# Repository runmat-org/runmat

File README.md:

<h1 align="center">RunMat</h1>

<p align="center">
  <strong>MATLAB-compatible runtime for fast GPU-accelerated math.</strong>
</p>

<p align="center">

</p>

<p align="center">
  <a href="https://runmat.com/sandbox"><strong>Try RunMat in your browser</strong></a>
  |
  <a href="https://runmat.com/download">Download RunMat Desktop</a>
  |
  <a href="https://runmat.com/docs">Docs</a>
  |
  <a href="docs/CHANGELOG.md">Changelog</a>
  |
  <a href="benchmarks/README.md">Benchmarks</a>
</p>

RunMat is a source-available, high-performance runtime designed for numerical computing using MATLAB-style syntax. It is built in Rust and provides a multi-tiered execution model that targets both CPU and GPU hardware without requiring manual management of tensor allocations and movement.

RunMat runs MATLAB-syntax `.m` files with automatic operation fusion, a high-performance compiler, and a cross-platform GPU backend powered by wgpu.

RunMat is free for eligible individuals, education, open-source projects and smaller organizations under the [RunMat Free Use grant](FREE-USE.md). Simulation allowances and subscription features are described on the [pricing page](https://runmat.com/pricing).

Key Capabilities:

- MATLAB Compatibility: Supports MATLAB-syntax scripts and projects, including arrays, functions, classes, packages, and [2,300+ documented built-in functions](https://runmat.com/docs/reference/builtins).
- Native Compilation: [Compile `.m` scripts into standalone native executables](https://runmat.com/docs/runtime/getting-started/cli#compile) with `runmat compile`.
- Code Checks and Tests: [Check code without executing it](https://runmat.com/docs/runtime/getting-started/cli#check) with `runmat check`, and [run MATLAB-style script, function, and class tests](https://runmat.com/docs/runtime/getting-started/cli#test-projects) with `runmat test`.
- Integer Support: Work with signed and unsigned integer types from 8 to 64 bits.
- Project Packages: [Manage dependencies and lockfiles](https://runmat.com/docs/runtime/packages) for reproducible MATLAB-syntax projects with the CLI.
- Automatic Fusion: Builds an internal graph of array operations to fuse elementwise math and reductions into optimized kernels 
- Tiered Execution: Combines a fast-startup VM interpreter with a JIT (based on Cranelift) for hot code paths
- Cross-Platform GPU: Transparently offloads workloads to Metal, DirectX 12, Vulkan, or WebGPU
- Strong Static Analysis: Type/shape inference, definite assignment, and other static analysis passes are run before execution to optimize the execution plan.
- Async Runtime: Built on Rust futures, allowing non-blocking execution in web environments, CLI tools and headless pipelines
- Integrated Plotting: Features an interactive GPU-accelerated 2D/3D plotting engine supporting 30+ plot types

Explore the [MATLAB compatibility guide](https://runmat.com/docs/runtime/matlab-compatibility) for supported language features, or use `runmat check analysis.m` to check your code before running it.

## Quick Start

The quickest way to get started is to [open the RunMat Sandbox](https://runmat.com/sandbox) and run code in your browser—no installation required. To work with local files, download [RunMat Desktop](https://runmat.com/download).

Alternatively, you can install the CLI:

```bash
# Linux/macOS
curl -fsSL https://runmat.com/install.sh | sh

# Windows PowerShell
iwr https://runmat.com/install.ps1 | iex
```

Create a script `hello.m`:

```matlab
disp("Hello, World!");
A = magic(3);
disp(sum(A));
```

Run the script:

```bash
runmat hello.m
```

See [Hello World](https://runmat.com/docs/runtime/getting-started/hello-world) for more examples, and the [Command Line Interface](https://runmat.com/docs/runtime/getting-started/cli) for the full command surface.

## Other Installation Options

```bash
# Homebrew (macOS/Linux)
brew install runmat-org/tap/runmat

# Cargo (Rust)
cargo install runmat --features gui

# Build from source
git clone https://github.com/runmat-org/runmat.git && cd runmat
cargo build -p runmat --release --features gui
```

## CLI

The CLI can run local scripts or named project entrypoints - on local or remote projects.

```bash
runmat analysis.m

# which is shorthand for:

runmat run analysis.m
```

Check an existing script, run your project's tests, or compile a script into a standalone native executable:

```bash
# Check code without executing it
runmat check analysis.m

# Run the project's MATLAB-style tests
runmat test

# Compile a script into a native executable
runmat compile analysis.m -o analysis
```

See [code checking](https://runmat.com/docs/runtime/getting-started/cli#check), [project tests](https://runmat.com/docs/runtime/getting-started/cli#test-projects), and [native compilation](https://runmat.com/docs/runtime/getting-started/cli#compile) for options and examples.

Projects can define named entrypoints in `runmat.toml`:

```toml
[package]
name = "demo"

[entrypoints.main]
path = "src/main.m"
```

Run the entrypoint:

```bash
runmat run main
```

### Project Testing and CI

Produce JUnit reports for CI and collect LCOV coverage:

```bash
runmat test --report junit
runmat test --coverage --coverage-format lcov
```

The test runner supports MATLAB-style script, function, and class tests, with name and tag filters, cancellation, and JSON, JUnit, or TAP reports. See [project testing](https://runmat.com/docs/runtime/getting-started/cli#test-projects).

### Cloud Project Files

To run a script in a remote project backend, ensure you are authenticated and have selected a project:

```bash
runmat login

# or explicitly specify the server URL

runmat login --server https://api.runmat.com

runmat project select <project-id>
```

And then run the script:

```bash
runmat remote run /scripts/analysis.m
```

The script is executed locally with the remote filesystem provider mounted into the runtime's filesystem abstraction. This means that mutations to the filesystem are persisted to the remote project, but the script runs locally.

For the full command surface, see [Command Line Interface](https://runmat.com/docs/runtime/getting-started/cli).

## TypeScript And WebAssembly

The `runmat` npm package embeds the runtime in browser, worker, Electron, and Node-based hosts.

```bash
npm install runmat
```

```ts
import { initRunMat } from "runmat";

const session = await initRunMat();

const result = await session.executeRequest({
  source: {
    kind: "text",
    name: "<repl>",
    text: "A = magic(3); disp(A)"
  }
});

console.log(result.stdout);
console.log(result.workspace.values);

session.dispose();
```

The TypeScript API includes session execution, workspace snapshots, lazy variable materialization, filesystem providers, plotting surfaces, stdout subscriptions, runtime diagnostics, and GPU status reporting.

See [bindings/ts/README.md](bindings/ts/README.md) and [WASM & TypeScript/JavaScript](docs/wasm/index.md).

## What Is In This Repository

| Area | Crates and paths |
| --- | --- |
| Language frontend | `runmat-lexer`, `runmat-parser`, `runmat-hir`, `runmat-mir`, `runmat-static-analysis` |
| Execution | `runmat-core`, `runmat-vm`, `runmat-runtime`, `runmat-builtins` |
| Native execution and compilation | `runmat-native-executor`, `runmat-jit`, `runmat-native-codegen`, `runmat-aot` |
| GPU acceleration | `runmat-accelerate`, `runmat-accelerate-api` |
| Memory management | `runmat-gc`, `runmat-gc-api` |
| Plotting | `runmat-plot` |
| Filesystem and config | `runmat-filesystem`, `runmat-config` |
| CLI and remote services | `runmat-cli`, `runmat-server-client` |
| Browser bindings | `runmat-wasm`, `bindings/ts` |
| Tooling | `runmat-lsp`, `runmat-telemetry`, `runmat-logging` |

The runtime is host-neutral. The CLI, Desktop, WASM bindings, and LSP all submit source through the same session/execution boundary and consume structured results.

## Runtime Highlights

- MATLAB-style source execution for scripts, functions, packages, imports, `classdef`, indexing, cells, structs, exceptions, and common language constructs.
- Built-in functions for array operations, linear algebra, tables, plotting, file I/O, optimization, and ODEs, plus control design with [`lqr`](https://runmat.com/docs/reference/builtins/lqr), linear regression with [`fitlm`](https://runmat.com/docs/reference/builtins/fitlm), spectral analysis with [`pwelch`](https://runmat.com/docs/reference/builtins/pwelch), and symbolic variables with [`syms`](https://runmat.com/docs/reference/builtins/syms).
- A bytecode VM for predictable startup and a Cranelift JIT for hot execution paths.
- GPU acceleration through fusion, auto-offload decisions, and `wgpu` backends for Metal, Vulkan, DirectX 12, and WebGPU.
- Interactive 2D and 3D plotting with figure handles, subplot state, labels, legends, export, replay, and browser canvas integration.
- Session APIs for REPLs, notebooks, editors, browser sandboxes, and remote filesystem-backed projects.
- TypeScript bindings with filesystem providers for memory, IndexedDB, and remote HTTP-backed workspaces.

### Validation

RunMat tests cover parsing and language semantics, runtime functions, CPU/GPU execution, and browser/WASM behavior. A shared workflow fixture exercises CSV import, MAT-file save/load, FFTs, filtering, and signal windows through both the CLI and WASM. See the [testing strategy](https://runmat.com/docs/runtime/development/testing) for the suites and commands used to validate these paths. For your own project, combine `runmat check` with representative runs and `runmat test` to verify the behavior your analysis depends on.

## GPU Acceleration

RunMat's acceleration engine captures array operations into fusion plans, estimates whether CPU or GPU execution is better for the current shapes, and keeps tensors resident on device when downstream work can reuse them.

```matlab
x = rand(10_000_000, 1, "single");
y = sin(x) .* exp(-x / single(10));
z = tanh(y) + single(0.1) .* y;
m = mean(z, "all");
```

Elementwise chains and reductions like this can be fused into larger GPU dispatches without writing kernel code. Smaller workloads can stay on CPU when transfer overhead would dominate.

See [GPU Acceleration & Fusion Engine](docs/gpu/index.md).

## Plotting

RunMat includes an open plotting engine used by the CLI, browser sandbox, and TypeScript bindings.

```matlab
x = 0:0.1:10;
plot(x, sin(x));
title("Sine wave");
grid on;
```

See [Plotting System](docs/plotting/index.md).

## Mechanical Design, Electrical Design and Simulation

RunMat 0.7.1 includes file-based engineering workflows alongside MATLAB-syntax
programs:

- Mechanical design uses `.part`, `.assembly` and `.drawing` files for
  parametric parts, assemblies, drawing views, dimensions and parts lists.
  See [Mechanical Design](docs/design/mcad/get-started.md).
- Electrical design uses `.circuit` and `.circuit.layout` files for schematics,
  board layouts and circuit simulation. See
  [Electrical Design](docs/design/ecad/get-started.md).
- FEA studies define geometry, materials, loads, constraints and solver settings
  in `.fea` files. See [Simulation](docs/simulation/index.md) for supported
  physics, examples and simulation-work measurement.

Mechanical design, electrical design and FEA are in beta. The guides describe
the supported workflows and their current limits. FEA meshing and solving
require sign-in, a connection to RunMat Server and an available simulation
allowance; ordinary local `.m` execution works offline.

## Documentation

Start here:

- [Installation](https://runmat.com/docs/runtime/getting-started/install)
- [Command Line Interface](https://runmat.com/docs/runtime/getting-started/cli)
- [Configuration Reference](https://runmat.com/docs/runtime/getting-started/config)
- [Hello World](https://runmat.com/docs/runtime/getting-started/hello-world)
- [MATLAB Language Compatibility](https://runmat.com/docs/runtime/matlab-compatibility)
- [Built-in Function Reference](https://runmat.com/docs/reference/builtins)
- [Project Packages](https://runmat.com/docs/runtime/packages)

Runtime internals:

- [Compilation Pipeline](docs/compiler/index.md)
- [Virtual Machine](docs/vm/index.md)
- [Runtime Values & Type Model](docs/VALUES.md)
- [Builtins](docs/builtins/index.md)
- [Session Engine](docs/session/index.md)
- [GPU Acceleration](docs/gpu/index.md)
- [JIT Compiler](docs/jit/index.md)
- [Filesystem Abstraction](docs/fs/index.md)
- [WebAssembly & TypeScript](docs/wasm/index.md)
- [Language Server Protocol](docs/lsp/index.md)
- [Development](docs/development/index.md)

The full docs index is [docs/README.md](docs/README.md).

## Benchmarks

The [benchmarks](benchmarks/README.md) directory contains reproducible cross-language comparisons against NumPy, PyTorch, Octave, and Julia where applicable.

Representative published runs include:

| Benchmark | Result |
| --- | --- |
| [Monte Carlo GBM risk simulation](benchmarks/monte-carlo-analysis/README.md) | Up to 131x faster than NumPy on the published sweep. |
| [Elementwise math](benchmarks/elementwise-math/README.md) | Up to 144x faster than PyTorch at 1B elements on the published sweep. |
| [4K image preprocessing](benchmarks/4k-image-processing/README.md) | Up to 10x faster than NumPy on the published sweep. |

Run the suite:

```bash
python3 benchmarks/.harness/run_suite.py \
  --suite benchmarks/.harness/suite.json \
  --output results/suite_results.json
```

Benchmark results depend on hardware, driver stack, backend selection, and workload shape. The benchmark harness records device details and parity checks with each run.

## Development

Install the Rust toolchain from `rust-toolchain.toml`, then build the workspace:

```bash
cargo build
cargo test
```

Build the CLI with plotting support:

```bash
cargo build -p runmat --release --features gui
```

Work on the TypeScript/WASM package:

```bash
cd bindings/ts
npm install
npm run build
npm test
```

Useful docs:

- [Build System](docs/development/build-system.md)
- [Testing Strategy](docs/development/testing.md)
- [Supported Architectures](docs/development/supported-architectures.md)
- [Benchmarking](docs/development/benchmarking.md)
- [Telemetry](docs/development/telemetry.md)

## License

RunMat is licensed under the [Business Source License 1.1](LICENSE.md) with the [RunMat Free Use grant](FREE-USE.md). Each version becomes available under Apache License 2.0 three years after it is first published. Releases through 0.6.2 retain their Apache License 2.0 terms.

RunMat is a trademark of Dystr, Inc. MATLAB is a registered trademark of The MathWorks, Inc. RunMat is not affiliated with, endorsed by, or sponsored by The MathWorks, Inc.

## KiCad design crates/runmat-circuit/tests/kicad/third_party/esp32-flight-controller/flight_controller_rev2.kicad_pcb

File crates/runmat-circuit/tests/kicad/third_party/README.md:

# Third-party KiCad boards

These are real KiCad 7 and 8 projects (board formats `20221018` and `20240108`) from other
authors. They are copied unchanged, and each one's license allows that.

- `tests/kicad_third_party.rs` reads each board, writes it back, and checks that the written
  file has the same tokens. It then exports the board from RunMat's own model and checks that
  every pad comes back where it was, on the same net.
- `tests/kicad_third_party_sch.rs` reads each schematic hierarchy into RunMat's model, checks
  that every part on the board is in it and that its nets are the board's pad nets, exports it
  back to KiCad and checks that the export reads back with the same parts and the same nets.
  The imports and the round trip pass the full design check.

| File | Board | Source | Commit | License |
|---|---|---|---|---|
| `atmega328p-datalogger-4l.kicad_pcb` | ATmega328P datalogger with 512 KB storage, 4 layers | [JMVI/KiCAD-PCB-Design-Examples](https://github.com/JMVI/KiCAD-PCB-Design-Examples), `ATMega328P-512K-Datalogger-4L/ATMega328P-512K-Datalogger-4L.kicad_pcb` | `d29c9ea257d068571b0bb1f7b1b92bac1368b5f1` | MIT, Copyright (c) 2025 Jaime Manuel Villegas Issa |
| `unipa-bioamp-pro.kicad_pcb` | UniPa BioAmp Pro, a biopotential (ECG/EMG/EEG) analog front end | [Mustafa-Yagci/unipa-bioamp-pro](https://github.com/Mustafa-Yagci/unipa-bioamp-pro), `hardware/UniPa_BioAmp_Pro.kicad_pcb` | `367965f53d1c62c64423019f24b6b5f661149be1` | MIT, Copyright (c) 2026 Mustafa Yağcı |
| `esp32-flight-controller/` (board and schematic, KiCad 8) | ESP32 drone flight controller, rev 2, 4 layers | [shazmeenShz/ESP32-Flight-Controller](https://github.com/shazmeenShz/ESP32-Flight-Controller), `Rev2/KiCad/flight_controller_rev2.kicad_pcb` and `.kicad_sch` | `d6dfbbb90a5bd5004c119a9a1ffc37b7ca904f28` | MIT, Copyright (c) 2026 Shazmeen Siddiqui |
| `ottercast-audio-v2/` (board and five schematic sheets, KiCad 7) | OtterCast Audio V2, a network audio receiver, 4 layers | [Ottercast/OtterCastAudioV2](https://github.com/Ottercast/OtterCastAudioV2), `OtterCastAudioV2.kicad_pcb`, `OtterCastAudioV2.kicad_sch`, `Audio.kicad_sch`, `MIPI.kicad_sch`, `Power.kicad_sch` and `WifiBT.kicad_sch` | `199395d7249aaf12432e42bff828dd665546d6a4` | MIT, Copyright (c) 2024 Ottercast, Jana Marie Hemsing |

Each MIT license asks that the copyright notice and the permission notice go with copies.
Here is the notice, which is the same in all four repositories apart from the copyright line:

> Permission is hereby granted, free of charge, to any person obtaining a copy of this software
> and associated documentation files (the "Software"), to deal in the Software without
> restriction, including without limitation the rights to use, copy, modify, merge, publish,
> distribute, sublicense, and/or sell copies of the Software, and to permit persons to whom the
> Software is furnished to do so, subject to the following conditions:
>
> The above copyright notice and this permission notice shall be included in all copies or
> substantial portions of the Software.
>
> THE SOFTWARE IS PROVIDED "AS IS", WITHOUT WARRANTY OF ANY KIND, EXPRESS OR IMPLIED, INCLUDING
> BUT NOT LIMITED TO THE WARRANTIES OF MERCHANTABILITY, FITNESS FOR A PARTICULAR PURPOSE AND
> NONINFRINGEMENT. IN NO EVENT SHALL THE AUTHORS OR COPYRIGHT HOLDERS BE LIABLE FOR ANY CLAIM,
> DAMAGES OR OTHER LIABILITY, WHETHER IN AN ACTION OF CONTRACT, TORT OR OTHERWISE, ARISING FROM,
> OUT OF OR IN CONNECTION WITH THE SOFTWARE OR THE USE OR OTHER DEALINGS IN THE SOFTWARE.

Before adding a board here, check its license file at the commit you copy from. Use only
permissive licenses: MIT, BSD, Apache-2.0, CC0 or CERN-OHL-P. Share-alike licenses such as
CC BY-SA, CERN-OHL-S and the GPL are not allowed. Then add a row to the table above.

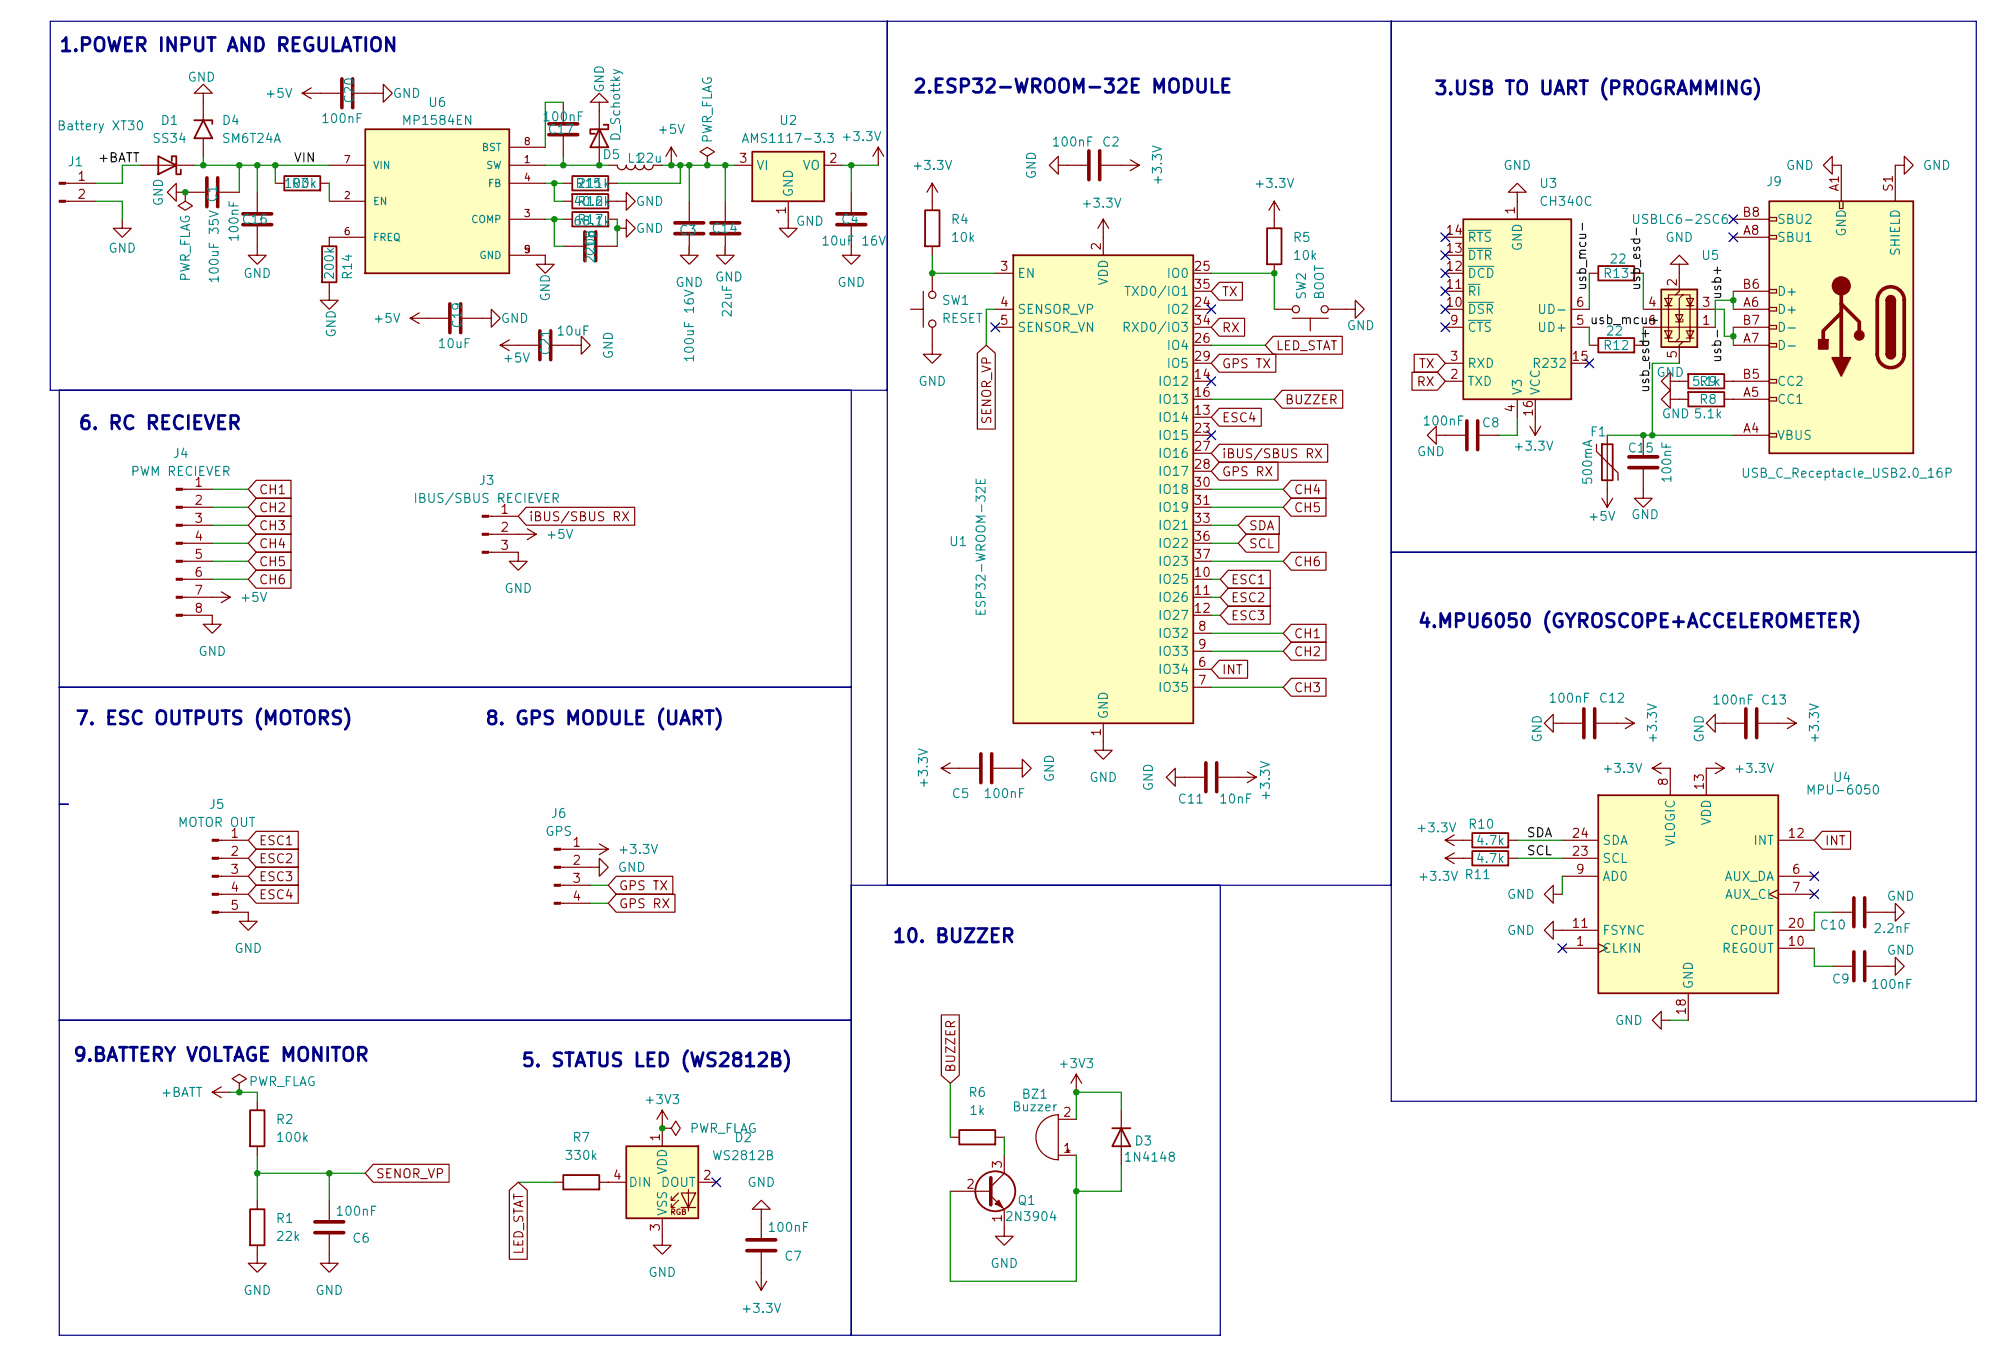
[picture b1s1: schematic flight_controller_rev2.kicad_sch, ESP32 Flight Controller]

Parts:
BZ1: Buzzer; Buzzer_12x9.5RM7.6
C1: 100uF 35V; C_Elec_8x10.2
C2, C5, C6, C7, C8, C9, C12, C13, C15, C16, C17, C20: 100nF; C_0603_1608Metric
C3: 100uF 16V; C_Elec_6.3x5.8
C4: 10uF 16V; C_0805_2012Metric
C10: 2.2nF; C_0603_1608Metric
C11: 10nF; C_0603_1608Metric
C14: 22uF; C_0805_2012Metric
C18: 220p; C_0603_1608Metric
C19, C21: 10uF; C_0805_2012Metric
D1: SS34; D_SMA
D2: WS2812B; LED_WS2812B_PLCC4_5.0x5.0mm_P3.2mm
D3: 1N4148; D_SOD-123
D4: SM6T24A; D_SMB
D5: D_Schottky; D_SMA
F1: 500mA; Fuse_1206_3216Metric
J1: Battery XT30; AMASS_XT30U-M_1x02_P5.0mm_Vertical
J3: IBUS/SBUS RECIEVER; PinHeader_1x03_P2.54mm_Vertical
J4: PWM RECIEVER; PinHeader_1x08_P2.54mm_Vertical
J5: MOTOR OUT; PinHeader_1x05_P2.54mm_Vertical
J6: GPS; PinHeader_1x04_P2.54mm_Vertical
J9: USB_C_Receptacle_USB2.0_16P; USB_C_Receptacle_GCT_USB4105-xx-A_16P_TopMnt_Horizontal
L1: 22u; L_Sunlord_SWPA6028S
Q1: 2N3904; SOT-23
R1: 22k; R_0603_1608Metric
R2, R3: 100k; R_0603_1608Metric
R4, R5: 10k; R_0603_1608Metric
R6: 1k; R_0603_1608Metric
R7: 330k; R_0603_1608Metric
R8, R9: 5.1k; R_0603_1608Metric
R10, R11: 4.7k; R_0603_1608Metric
R12, R13: 22; R_0603_1608Metric
R14: 200k; R_0603_1608Metric
R15: 211k; R_0603_1608Metric
R16: 40.2k; R_0603_1608Metric
R17: 68.1k; R_0603_1608Metric
SW1: RESET; SW_Push_1P1T_XKB_TS-1187A
SW2: BOOT; SW_Push_1P1T_XKB_TS-1187A
U1: ESP32-WROOM-32E; ESP32-WROOM-32D
U2: AMS1117-3.3; SOT-223-3_TabPin2
U3: CH340C; SOIC-16_3.9x9.9mm_P1.27mm
U4: MPU-6050; InvenSense_QFN-24_4x4mm_P0.5mm
U5: USBLC6-2SC6; SOT-23-6
U6: MP1584EN; SOIC-8-1EP_3.9x4.9mm_P1.27mm_EP2.29x3mm

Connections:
+3.3V: C2.1, C4.1, C5.1, C7.1, C11.1, C12.1, C13.1, J6.1, R4.1, R5.1, R10.1, R11.1, U1.2 (VDD), U2.2 (VO), U3.16 (VCC), U4.8 (VLOGIC), U4.13 (VDD)
+3V3: BZ1.2 (-), D2.1 (VDD), D3.1 (K)
+5V: C3.1, C14.1, C19.1, C20.1, C21.1, F1.2, J3.2, J4.7, L1.1, R15.2, U2.3 (VI)
+BATT: D1.2 (A), J1.1, R2.1
/VIN: C1.2, C16.1, D1.1 (K), D4.2 (A2), R3.1, U6.7 (VIN)
/usb+: J9.A6 (D+), J9.B6 (D+), U5.1 (I/O1)
/usb-: J9.A7 (D-), J9.B7 (D-), U5.3 (I/O2)
/usb_esd-: R13.2, U5.4 (I/O2)
/usb_mcu+: R12.1, U3.5 (UD+)
/usb_mcu-: R13.1, U3.6 (UD-)
BUZZER: R6.1, U1.16 (IO13)
CH1: J4.1, U1.8 (IO32)
CH2: J4.2, U1.9 (IO33)
CH3: J4.3, U1.7 (IO35)
CH4: J4.4, U1.30 (IO18)
CH5: J4.5, U1.31 (IO19)
CH6: J4.6, U1.37 (IO23)
ESC1: J5.1, U1.10 (IO25)
ESC2: J5.2, U1.11 (IO26)
ESC3: J5.3, U1.12 (IO27)
ESC4: J5.4, U1.13 (IO14)
GND: C1.1, C2.2, C3.2, C4.2, C5.2, C6.1, C7.2, C8.2, C9.2, C10.2, C11.2, C12.2, C13.2, C14.2, C15.2, C16.2, C18.2, C19.2, C20.2, C21.2, D2.3 (VSS), D4.1 (A1), D5.1 (K), J1.2, J3.3, J4.8, J5.5, J6.2, J9.A1 (GND), J9.A12 (GND), J9.B1 (GND), J9.B12 (GND), J9.S1 (SHIELD), Q1.1 (E), R1.2, R8.2, R9.2, R14.2, R16.1, R17.2, SW1.1, SW2.1, U1.1 (GND), U1.15 (GND), U1.38 (GND), U1.39 (GND), U2.1 (GND), U3.1 (GND), U4.9 (AD0), U4.11 (FSYNC), U4.18 (GND), U5.2 (GND), U6.5 (GND), U6.9 (GND)
GPS RX: J6.4, U1.28 (IO17)
GPS TX: J6.3, U1.29 (IO5)
INT: U1.6 (IO34), U4.12 (INT)
LED_STAT: R7.1, U1.26 (IO4)
unnamed: BZ1.1 (+), D3.2 (A), Q1.2 (B)
unnamed: D2.4 (DIN), R7.2
unnamed: C17.2, D5.2 (A), L1.2, U6.1 (SW)
unnamed: J9.A5 (CC1), R8.1
unnamed: J9.B5 (CC2), R9.1
unnamed: Q1.3 (C), R6.2
unnamed: R12.2, U5.6 (I/O1)
unnamed: R4.2, SW1.2, U1.3 (EN)
unnamed: R5.2, SW2.2, U1.25 (IO0)
unnamed: C8.1, U3.4 (V3)
unnamed: C10.1, U4.20 (CPOUT)
unnamed: C9.1, U4.10 (REGOUT)
unnamed: C15.1, F1.1, J9.A4 (VBUS), J9.A9 (VBUS), J9.B4 (VBUS), J9.B9 (VBUS), U5.5 (VBUS)
unnamed: C17.1, U6.8 (BST)
unnamed: C18.1, R17.1, U6.3 (COMP)
unnamed: R3.2, U6.2 (EN)
unnamed: R15.1, R16.2, U6.4 (FB)
unnamed: R14.1, U6.6 (FREQ)
RX: U1.34 (RXD0/IO3), U3.2 (TXD)
SCL: R11.2, U1.36 (IO22), U4.23 (SCL)
SDA: R10.2, U1.33 (IO21), U4.24 (SDA)
SENOR_VP: C6.2, R1.1, R2.2, U1.4 (SENSOR_VP)
TX: U1.35 (TXD0/IO1), U3.3 (RXD)
iBUS/SBUS RX: J3.1, U1.27 (IO16)

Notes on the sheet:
7. ESC OUTPUTS (MOTORS)
9.BATTERY VOLTAGE MONITOR
2.ESP32-WROOM-32E MODULE
3.USB TO UART (PROGRAMMING)
10. BUZZER
4.MPU6050 (GYROSCOPE+ACCELEROMETER)
6. RC RECIEVER
8. GPS MODULE (UART)
5. STATUS LED (WS2812B)
1.POWER INPUT AND REGULATION

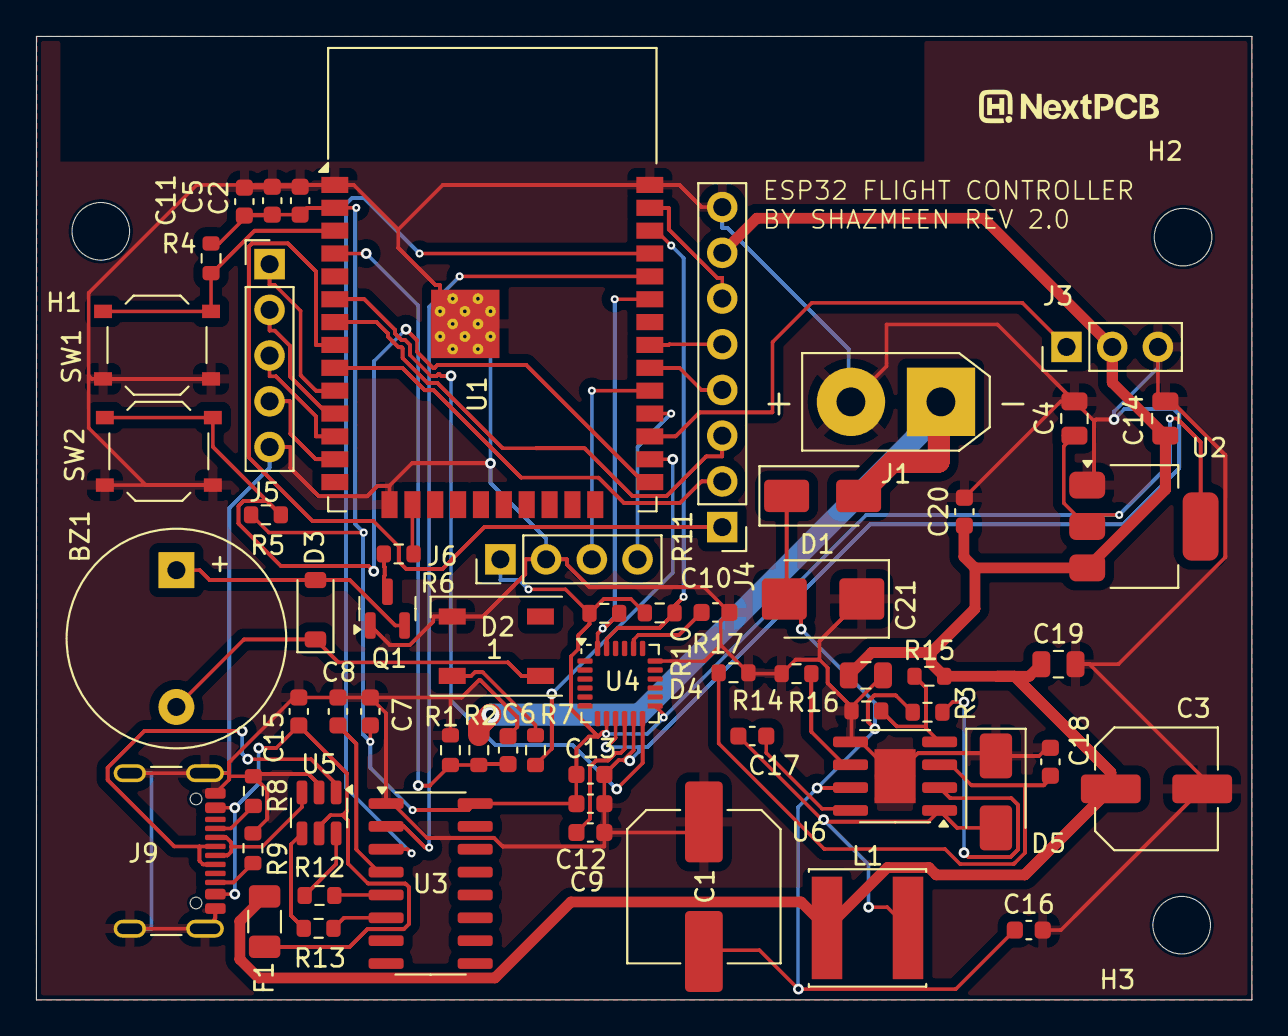
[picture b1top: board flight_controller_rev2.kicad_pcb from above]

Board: 4 copper layers, 67.5 x 53.5 mm, 64 parts (0 on the bottom side), 50 nets.

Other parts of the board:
H1, H2, H3: MountingHole_3.2mm_M3

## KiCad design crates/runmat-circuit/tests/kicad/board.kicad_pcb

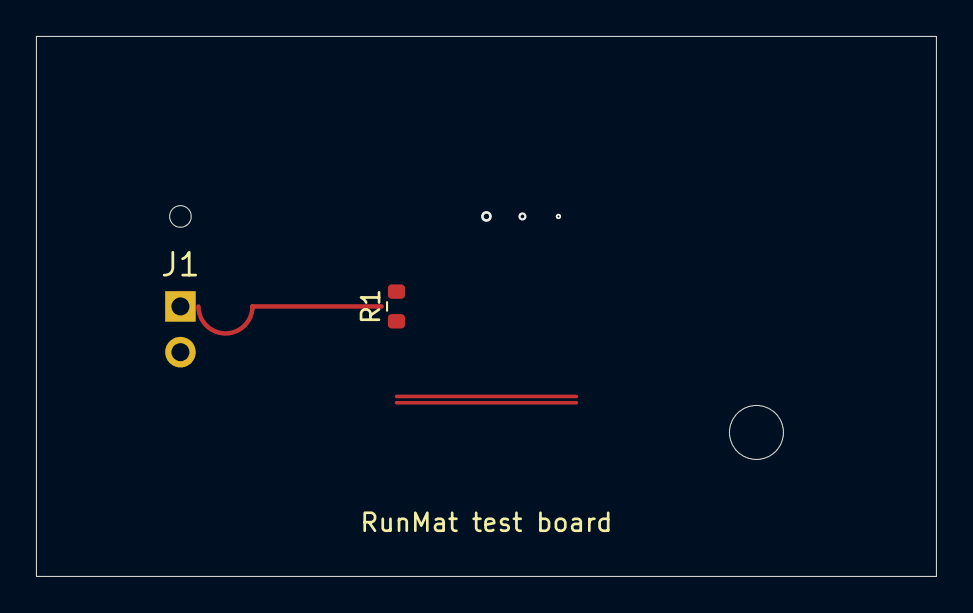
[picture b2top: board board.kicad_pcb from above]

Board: 4 copper layers, 50.0 x 30.0 mm, 3 parts (1 on the bottom side), 2 nets.

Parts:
C1: 100n; C_0805_2012Metric
J1: Conn; PinHeader_1x02_P2.54mm_Vertical
R1: 10k; R_0603_1608Metric

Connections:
GND: C1.2, J1.2, R1.2
VCC: C1.1, J1.1

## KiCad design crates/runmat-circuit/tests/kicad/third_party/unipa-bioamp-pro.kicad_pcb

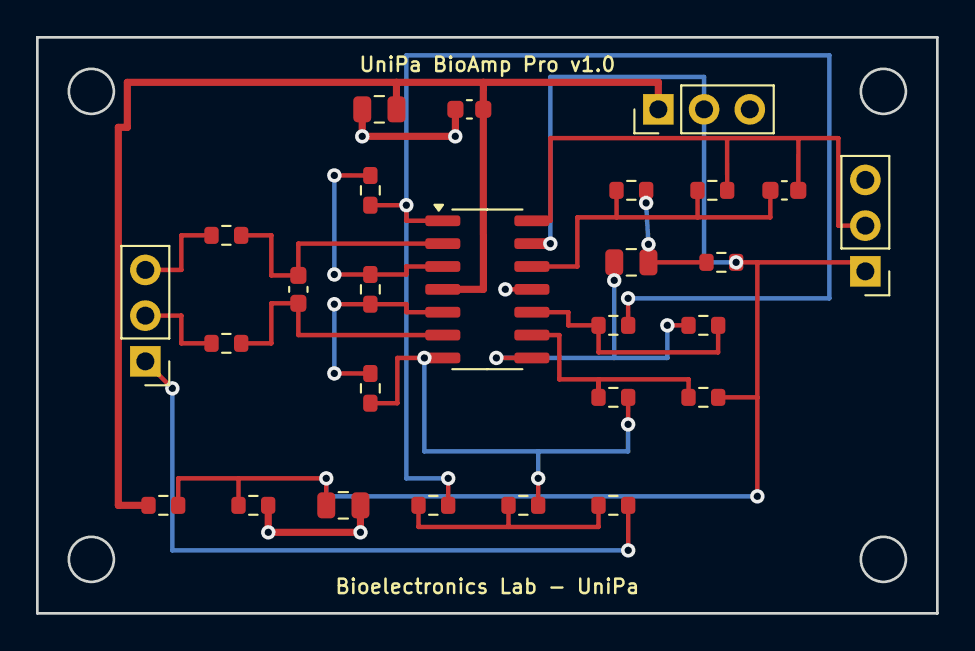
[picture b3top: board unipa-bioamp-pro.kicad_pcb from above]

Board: 2 copper layers, 50.0 x 32.0 mm, 27 parts (0 on the bottom side), 19 nets.

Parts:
C1: 1nF; C_0603_1608Metric
C2: 1uF_HPF; C_0805_2012Metric
C3, C6: 100nF; C_0603_1608Metric
C4, C5: 10uF; C_0805_2012Metric
J1: ELECTRODES_IN; PinHeader_1x03_P2.54mm_Vertical
J2: BIOAMP_OUTPUT; PinHeader_1x03_P2.54mm_Vertical
J3: POWER_IN; PinHeader_1x03_P2.54mm_Vertical
R1, R2, R11: 10k; R_0603_1608Metric
R3: 10k_Rg; R_0603_1608Metric
R4, R5: 47k; R_0603_1608Metric
R6, R7, R8, R9, R13, R14, R15, R16: 100k; R_0603_1608Metric
R10: 330k; R_0603_1608Metric
R12: 1M; R_0603_1608Metric
R17: 100k_Safe; R_0603_1608Metric
U1: TL074; SOIC-14_3.9x8.7mm_P1.27mm

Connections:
/BIO_OUT: C3.1, J2.2, R12.1, U1.14
/DRL_ELEC: J1.1, R17.1
/ELEC_IN+: J1.3, R1.2
/ELEC_IN-: J1.2, R2.2
/INA_OUT: C2.2, R8.1, U1.8
/VREF: C4.1, J2.1, J3.2, R9.1, R10.2, R13.2, R14.1, U1.13
GND: C4.2, C5.2, C6.2, J2.3, J3.3, R14.2, U1.11
unnamed: C2.1, R10.1, R11.2
unnamed: R15.1, R16.1, R17.2
unnamed: R4.1, R6.2, R15.2, U1.1
unnamed: R5.1, R7.2, R16.2, U1.7
unnamed: R3.1, R4.2, U1.3
unnamed: C1.1, R1.1, U1.2
unnamed: R3.2, R5.2, U1.5
unnamed: C1.2, R2.1, U1.6
unnamed: R6.1, R8.2, U1.10
unnamed: R7.1, R9.2, U1.9
unnamed: C3.2, R11.1, R12.2, U1.12
VCC: C5.1, C6.1, J3.1, R13.1, U1.4

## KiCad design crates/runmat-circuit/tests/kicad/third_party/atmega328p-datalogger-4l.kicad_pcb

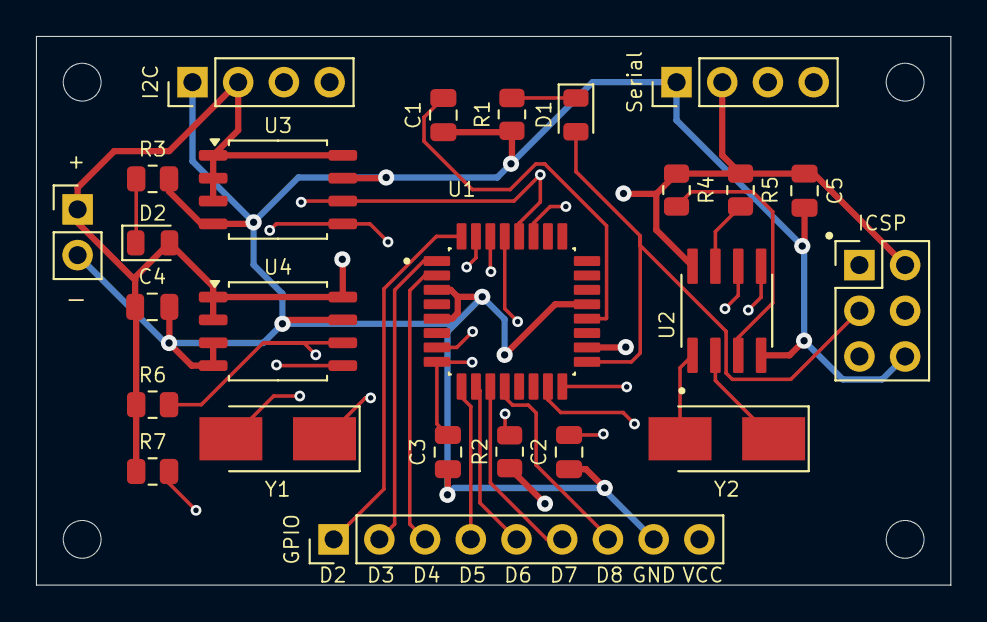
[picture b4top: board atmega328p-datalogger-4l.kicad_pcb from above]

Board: 4 copper layers, 50.8 x 30.5 mm, 29 parts (0 on the bottom side), 26 nets.

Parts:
BT1: Battery; PinHeader_1x02_P2.54mm_Vertical
C1, C5: 0.1u; C_0805_2012Metric
C2, C3: 22p; C_0805_2012Metric
C4: 100n; C_0805_2012Metric
D1, D2: LED; LED_0805_2012Metric
GPIO: Conn_01x09_Pin; PinHeader_1x09_P2.54mm_Vertical
H1, H2, H3, H4: MountingHole; MountingHole_2.1mm
I2C: Conn_01x04_Pin; PinHeader_1x04_P2.54mm_Vertical
ICSP: Conn_02x03_Odd_Even; PinHeader_2x03_P2.54mm_Vertical
R1, R3: 330; R_0805_2012Metric
R2, R4, R5: 10K; R_0805_2012Metric
R6, R7: 4.7K; R_0805_2012Metric
Serial: Conn_01x04_Pin; PinHeader_1x04_P2.54mm_Vertical
U1: ATMEGA328P-AU; QFP80P900X900X120-32N
U2: DS1337S_; SOIC127P600X175-8N
U3, U4: 24LC1025; SOIC-8_5.23x5.23mm_P1.27mm
Y1: 16 MHz; Crystal_SMD_5032-2Pin_5.0x3.2mm_HandSoldering
Y2: 32.768 KHz; Crystal_SMD_5032-2Pin_5.0x3.2mm_HandSoldering

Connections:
/D2: GPIO.1, U1.32 (PD2)
/D3: GPIO.2, U1.1 (PD3)
/D4: GPIO.3, U1.2 (PD4)
/D5: GPIO.4, U1.9 (PD5)
/D6: GPIO.5, U1.10 (PD6)
/D7: GPIO.6, U1.11 (PD7)
/D8: GPIO.7, U1.12 (PB0)
/MISO: ICSP.1, U1.16 (PB4)
/MOSI: ICSP.4, U1.15 (PB3)
/RESET: ICSP.5, R2.2, U1.29 (PC6/~RESET)
/RX: Serial.4, U1.30 (PD0)
/SCK: D1.2 (A), ICSP.3, U1.17 (PB5)
/SCL: I2C.4, R6.2, U1.28 (PC5), U2.6 (SCL), U3.6 (SCL), U4.6 (SCL)
/SDA: I2C.3, R7.2, U1.27 (PC4), U2.5 (SDA), U3.5 (SDA), U4.5 (SDA)
/TX: Serial.3, U1.31 (PD1)
/VCC: BT1.1 (+), C4.1, C5.1, D2.2 (A), GPIO.9, I2C.2, ICSP.2, R2.1, R4.1, R5.1, R6.1, R7.1, Serial.2, U1.18 (AVCC), U2.8 (VCC), U3.1 (A0), U3.2 (A1), U3.3 (A2), U3.8 (VCC), U4.1 (A0), U4.2 (A1), U4.8 (VCC)
GND: BT1.2 (-), C1.1, C2.1, C3.1, C4.2, C5.2, GPIO.8, I2C.1, ICSP.6, R1.1, R3.2, Serial.1, U1.3 (GND), U1.5 (GND), U1.21 (GND), U2.4 (GND), U3.4 (GND), U3.7 (WP), U4.3 (A2), U4.4 (GND), U4.7 (WP)
unnamed: D1.1 (K), R1.2
unnamed: D2.1 (K), R3.1
unnamed: C1.2, U1.20 (AREF)
unnamed: C2.2, U1.7 (PB6), Y1.2
unnamed: C3.2, U1.8 (PB7), Y1.1
unnamed: R5.2, U2.7 (SQW/~INT)
unnamed: U2.1 (X1), Y2.2
unnamed: U2.2 (X2), Y2.1
unnamed: R4.2, U2.3 (~INTA)

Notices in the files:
README.md:
License: BSL-1.1
crates/runmat-circuit/tests/kicad/third_party/esp32-flight-controller/flight_controller_rev2.kicad_pcb:
© 2026
